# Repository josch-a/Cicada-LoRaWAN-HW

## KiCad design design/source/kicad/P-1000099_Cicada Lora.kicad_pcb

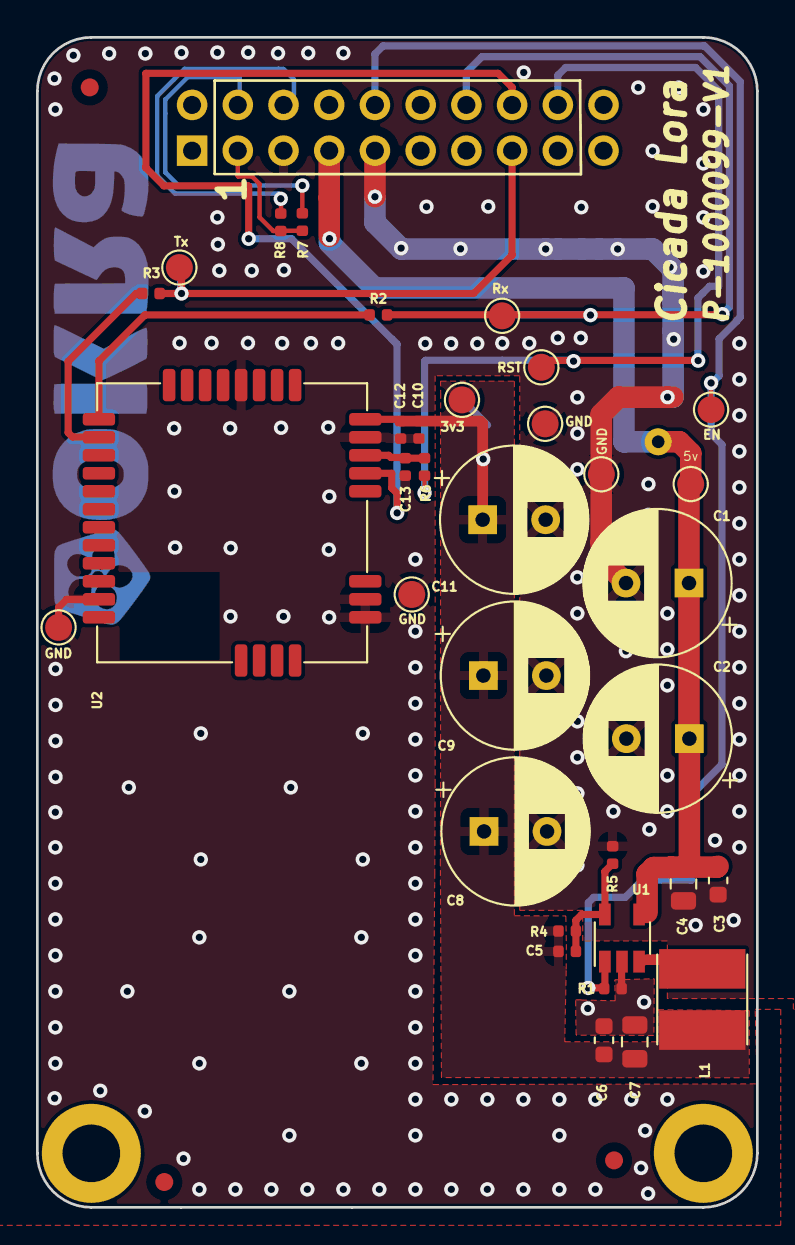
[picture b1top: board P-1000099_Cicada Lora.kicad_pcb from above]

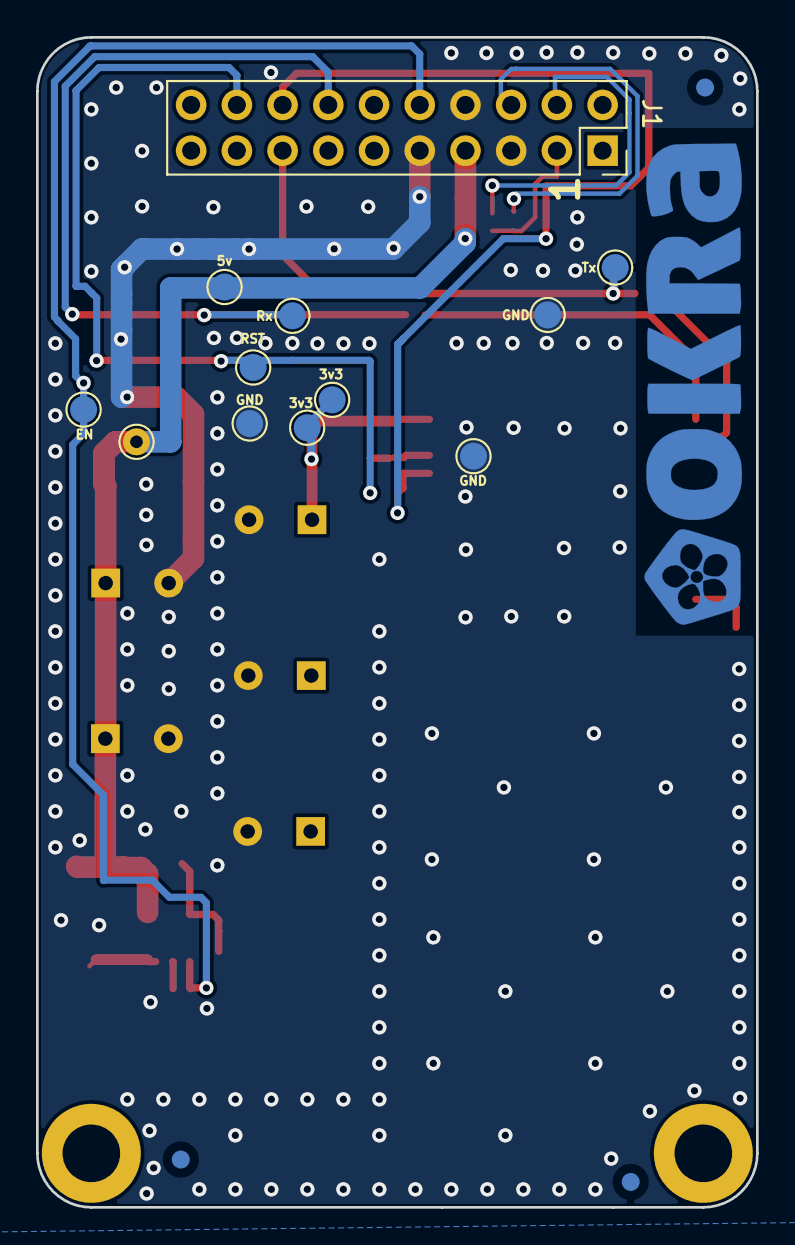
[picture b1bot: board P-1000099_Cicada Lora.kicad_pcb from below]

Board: 2 copper layers, 40.0 x 65.0 mm, 55 parts (16 on the bottom side), 16 nets.

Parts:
C1, C2, C8, C9, C11: 1000uF 10v; CP_Radial_D8.0mm_P3.50mm
C3, C6: 100nF 16v X7R; C_0603_1608Metric
C4, C7: 10uF 16v X7R; C_0805_2012Metric
C5: 100pF C0G; C_0402_1005Metric
C10, C13: 100nF 10v X5R; C_0402_1005Metric
C12: 10uF 10v X5R; C_0402_1005Metric
FID1, FID2, FID3, FID4, FID5, FID6: Fiducial; Fiducial_1mm_Mask2mm
H1, H2: MountingHole_Pad; MountingHole_3.2mm_M3_ISO14580_Pad
J1: Host; PinSocket_2x08_P2.54mm_Vertical_padded
L1: 3.3uH 2A; L_4030_Handsoldering
LOGO1: SYM_Hot_Small; okra_logo_copper_2
R1, R4: 40.2k; R_0402_1005Metric
R2, R3: 22R; R_0402_1005Metric
R5: 8.87k; R_0402_1005Metric
R6: 10K; R_0402_1005Metric
R7: 22.6K; R_0402_1005Metric
R8: 86.6k; R_0402_1005Metric
TP1, TP3: 5v; TestPoint_Pad_D1.5mm
TP2: 5v; TestPoint_THTPad_D1.5mm_Drill0.7mm
TP3#2, TP8, TP11, TP13, TP16, TP17, TP39: GND; TestPoint_Pad_D1.5mm
TP4, TP6: Tx; TestPoint_Pad_D1.5mm
TP5, TP7: Rx; TestPoint_Pad_D1.5mm
TP9, TP15: RST; TestPoint_Pad_D1.5mm
TP10, TP12, TP14: 3v3; TestPoint_Pad_D1.5mm
TP18, TP19: EN; TestPoint_Pad_D1.5mm
U1: HX3406; TSOT-23-5
U2: RAK3172(H); Lora

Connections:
/3V3: C5.1, C6.1, C7.1, C8.1, C9.1, C10.2, C11.1, C12.2, L1.2, R4.1, TP10.1, TP12.1, TP14.1, U2.24 (3V3)
/5V0: C1.1, C2.1, C3.1, C4.1, J1.5, TP1.1, TP2.1, TP3.1, U1.4 (VIN)
/BOOT: J1.14, U2.21 (BOOT)
/POWER_EN: J1.8, R1.1, TP18.1, TP19.1, U1.1 (RUN)
/UART_RX_3v3: J1.12, R2.1, TP5.1, TP7.1
/UART_TX_3v3: J1.13, R3.1, TP4.1, TP6.1
/VER_1: J1.2, R7.2
/VER_2: J1.4, R8.2
/Vref(3V3): J1.1, R7.1, R8.1
/nRST: J1.16, R6.1, TP9.1, TP15.1
GND: C1.2, C2.2, C3.2, C4.2, C6.2, C7.2, C8.2, C9.2, C10.1, C11.2, C12.1, C13.1, J1.3, J1.6, J1.7, R1.2, R5.2, TP3#2.1, TP8.1, TP11.1, TP13.1, TP16.1, TP17.1, TP39.1, U1.2 (GND), U2.11 (GND), U2.17 (GND), U2.18 (GND), U2.23 (GND), U2.28 (GND)
unnamed: C5.2, R4.2, R5.1, U1.5 (VOUT)
unnamed: C13.2, R6.2, U2.22 (RST)
unnamed: L1.1, U1.3 (SW)
unnamed: R2.2, U2.1 (UART2_Rx)
unnamed: R3.2, U2.2 (UART2_Tx)

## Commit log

2026-03-27 initial creation
